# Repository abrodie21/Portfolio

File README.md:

# Design Portfolio

Here are two designs of personal projects that I have completed during my undergrad.

Design 1: Heartbeat Detection device, utilizing an IR emitter/sensor to measure the density of blood in a finger, signal processing to blink an LED with the hearbeat.

-This project was originally a Circuits II Lab project at Purdue (2k8) that I expanded upon to include a PCB schematic that can be fabricated.

Design 2: Powered Device sensor, utilizing a differential coil setup to detect magnetic fields in close proximity generated by transformers in power adapters. 

-Designed to be cheap and cost effective, utilizing a 1 layer PCB and as few components as possible.

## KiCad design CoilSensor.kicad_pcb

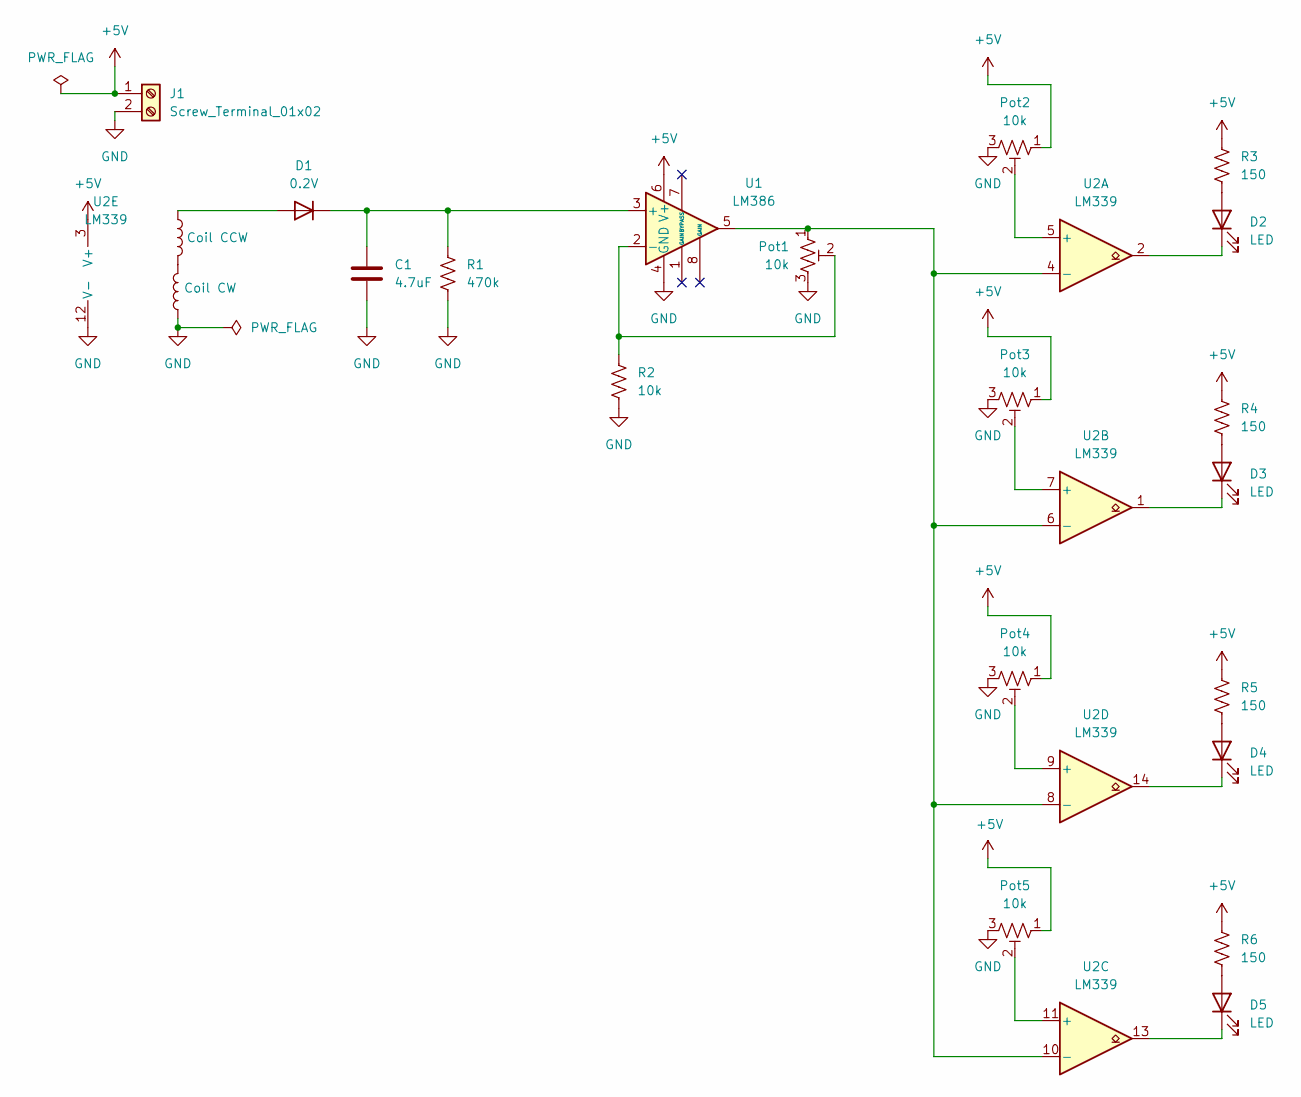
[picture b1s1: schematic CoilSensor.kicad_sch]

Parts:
C1: 4.7uF; CP_Elec_8x10.5
D1: 0.2V; D_5KPW_P7.62mm_Vertical_AnodeUp
D2, D3, D4, D5: LED; D_5KPW_P7.62mm_Vertical_AnodeUp
J1: Screw_Terminal_01x02; TerminalBlock_4Ucon_1x02_P3.50mm_Vertical
L1, L2: 2Pad
Pot1, Pot2, Pot3, Pot4, Pot5: 10k; Potentiometer_Vishay_T73XW_Horizontal
R1: 470k; R_Axial_DIN0414_L11.9mm_D4.5mm_P20.32mm_Horizontal
R2: 10k; R_Axial_DIN0414_L11.9mm_D4.5mm_P20.32mm_Horizontal
R3, R4, R5, R6: 150; R_Axial_DIN0414_L11.9mm_D4.5mm_P20.32mm_Horizontal
U1: LM386; DIP-8_W7.62mm_Socket_LongPads
U2: LM339; DIP-14_W7.62mm

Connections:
+5V: J1.1, Pot2.1, Pot3.1, Pot4.1, Pot5.1, R3.1, R4.1, R5.1, R6.1, U1.6 (V+), U2.3 (V+)
GND: C1.2, J1.2, L2.1, Pot1.3, Pot2.3, Pot3.3, Pot4.3, Pot5.3, R1.2, R2.2, U1.4 (GND), U2.12 (V-)
unnamed: D1.2 (A), L1.1
unnamed: C1.1, D1.1 (K), R1.1, U1.3 (+)
unnamed: D2.2 (A), R3.2
unnamed: D2.1 (K), U2.2
unnamed: D3.2 (A), R4.2
unnamed: D3.1 (K), U2.1
unnamed: D4.2 (A), R5.2
unnamed: D4.1 (K), U2.14
unnamed: D5.2 (A), R6.2
unnamed: D5.1 (K), U2.13
unnamed: L1.2, L2.2
unnamed: Pot1.2, R2.1, U1.2 (-)
unnamed: Pot2.2, U2.5 (+)
unnamed: Pot1.1, U1.5, U2.4 (-), U2.6 (-), U2.8 (-), U2.10 (-)
unnamed: Pot3.2, U2.7 (+)
unnamed: Pot5.2, U2.11 (+)
unnamed: Pot4.2, U2.9 (+)

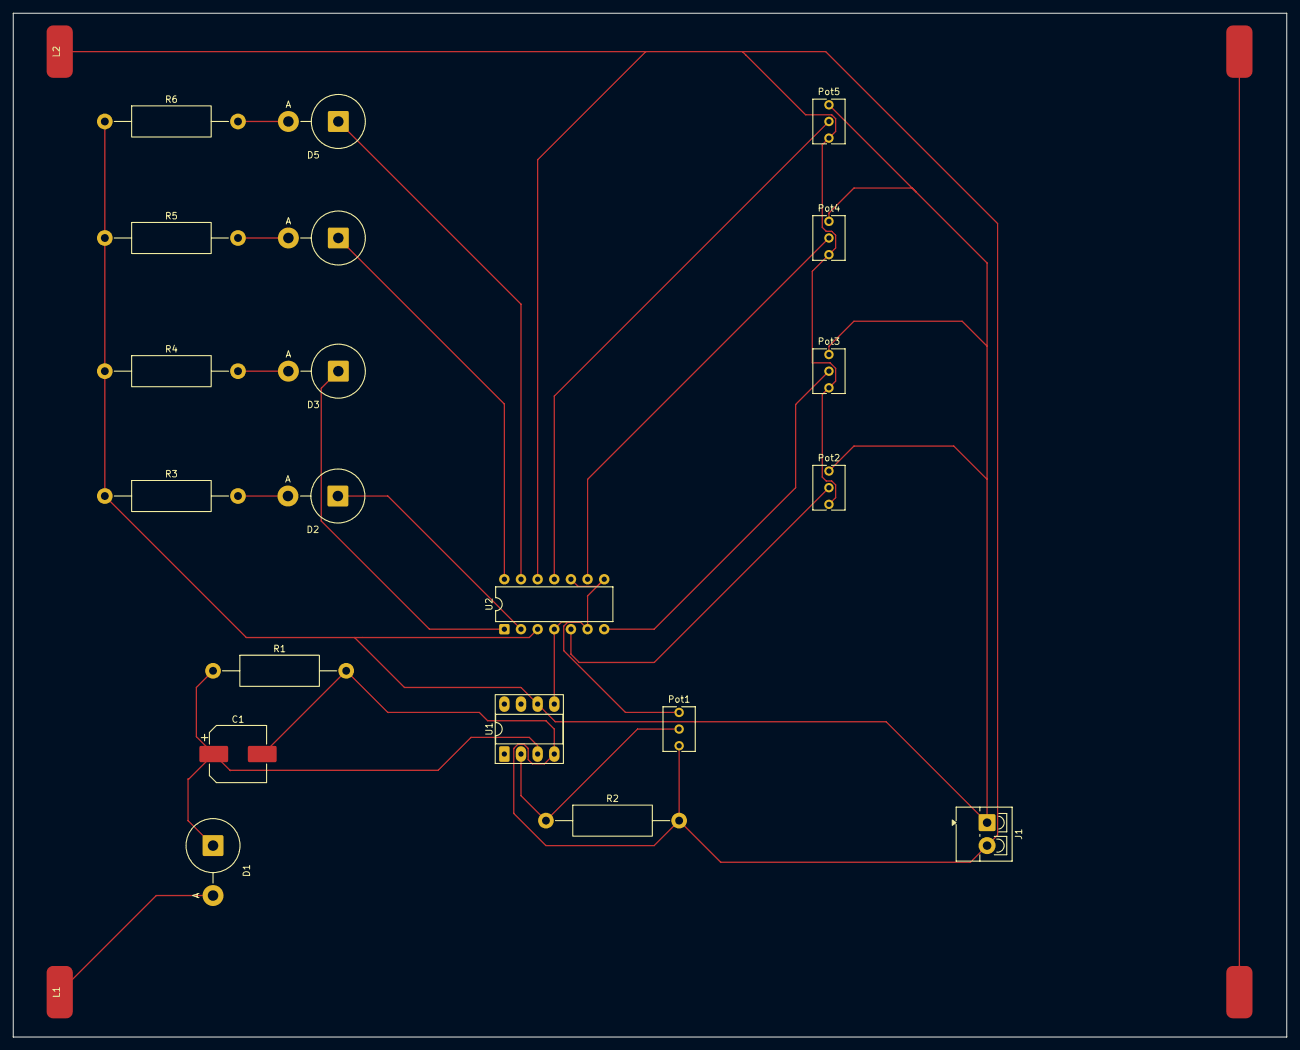
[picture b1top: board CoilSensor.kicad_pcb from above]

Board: 2 copper layers, 194.3 x 156.2 mm, 22 parts (0 on the bottom side), 19 nets.

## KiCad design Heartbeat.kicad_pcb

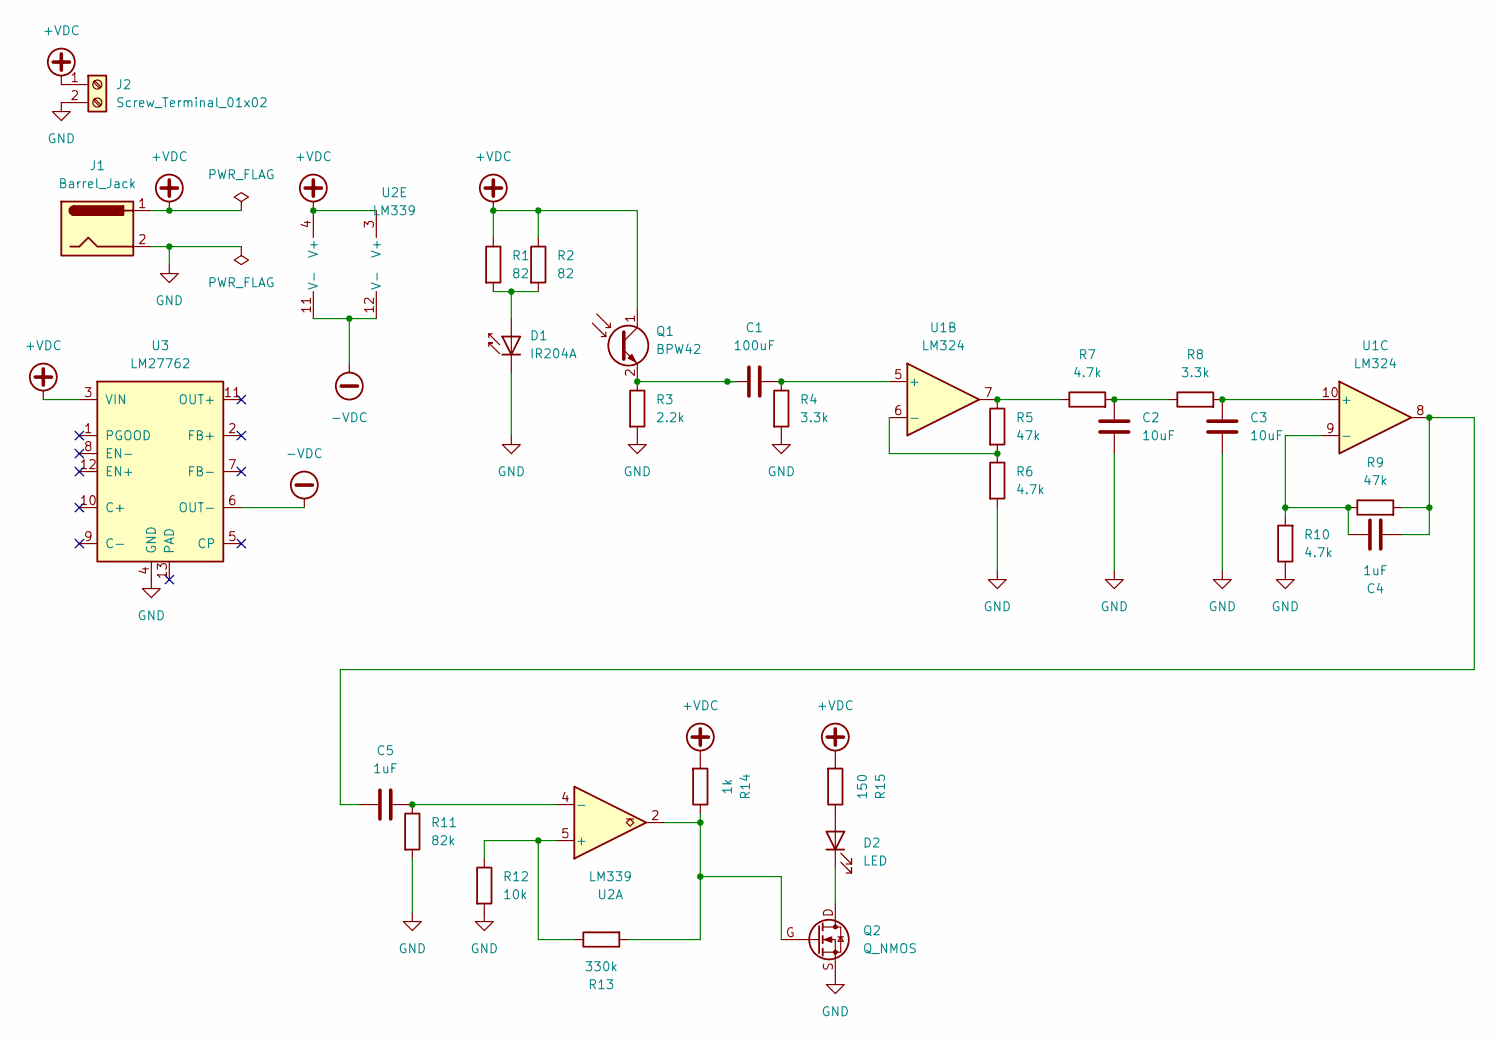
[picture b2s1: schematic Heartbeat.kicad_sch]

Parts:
C1: 100uF; CP_Axial_L11.0mm_D5.0mm_P18.00mm_Horizontal
C2, C3: 10uF; CP_Axial_L11.0mm_D5.0mm_P18.00mm_Horizontal
C4, C5: 1uF; CP_Axial_L11.0mm_D5.0mm_P18.00mm_Horizontal
D1: IR204A; D_DO-41_SOD81_P2.54mm_Vertical_AnodeUp
D2: LED; D_DO-41_SOD81_P2.54mm_Vertical_AnodeUp
J1: Barrel_Jack; BarrelJack_CUI_PJ-063AH_Horizontal_CircularHoles
J2: Screw_Terminal_01x02; TerminalBlock_4Ucon_1x02_P3.50mm_Vertical
Q1: BPW42; D_DO-41_SOD81_P2.54mm_Vertical_AnodeUp
Q2: Q_NMOS; TO-251-3_Vertical
R1, R2: 82; R_Axial_DIN0204_L3.6mm_D1.6mm_P5.08mm_Horizontal
R3: 2.2k; R_Axial_DIN0204_L3.6mm_D1.6mm_P5.08mm_Horizontal
R4, R8: 3.3k; R_Axial_DIN0204_L3.6mm_D1.6mm_P5.08mm_Horizontal
R5, R9: 47k; R_Axial_DIN0204_L3.6mm_D1.6mm_P5.08mm_Horizontal
R6, R7, R10: 4.7k; R_Axial_DIN0204_L3.6mm_D1.6mm_P5.08mm_Horizontal
R11: 82k; R_Axial_DIN0204_L3.6mm_D1.6mm_P5.08mm_Horizontal
R12: 10k; R_Axial_DIN0204_L3.6mm_D1.6mm_P5.08mm_Horizontal
R13: 330k; R_Axial_DIN0204_L3.6mm_D1.6mm_P5.08mm_Horizontal
R14: 1k; R_Axial_DIN0204_L3.6mm_D1.6mm_P5.08mm_Horizontal
R15: 150; R_Axial_DIN0204_L3.6mm_D1.6mm_P5.08mm_Horizontal
U1: LM324; DIP-14_W7.62mm
U2: LM339; SOIC-14_3.9x8.7mm_P1.27mm
U3: LM27762; WSON-12-1EP_3x2mm_P0.5mm_EP1x2.65_ThermalVias

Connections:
+VDC: J1.1, J2.1, Q1.1 (C), R1.1, R2.1, R14.2, R15.2, U1.4 (V+), U2.3 (V+), U3.3 (VIN)
-VDC: U1.11 (V-), U2.12 (V-), U3.6 (OUT-)
GND: C2.1, C3.1, D1.1 (K), J1.2, J2.2, Q2.S, R3.2, R4.2, R6.2, R10.1, R11.2, R12.2, U3.4 (GND); also elsewhere on the board
unnamed: C2.2, R7.2, R8.1
unnamed: C4.1, C5.1, R9.2, U1.8
unnamed: D1.2 (A), R1.2, R2.2
unnamed: D2.2 (A), R15.1
unnamed: D2.1 (K), Q2.D
unnamed: C1.1, Q1.2 (E), R3.1
unnamed: Q2.G, R13.2, R14.1, U2.2
unnamed: R5.1, R7.1, U1.7
unnamed: C1.2, R4.1, U1.5 (+)
unnamed: R5.2, R6.1, U1.6 (-)
unnamed: C3.2, R8.2, U1.10 (+)
unnamed: C4.2, R9.1, R10.2, U1.9 (-)
unnamed: R12.1, R13.1, U2.5 (+)
unnamed: C5.2, R11.1, U2.4 (-)

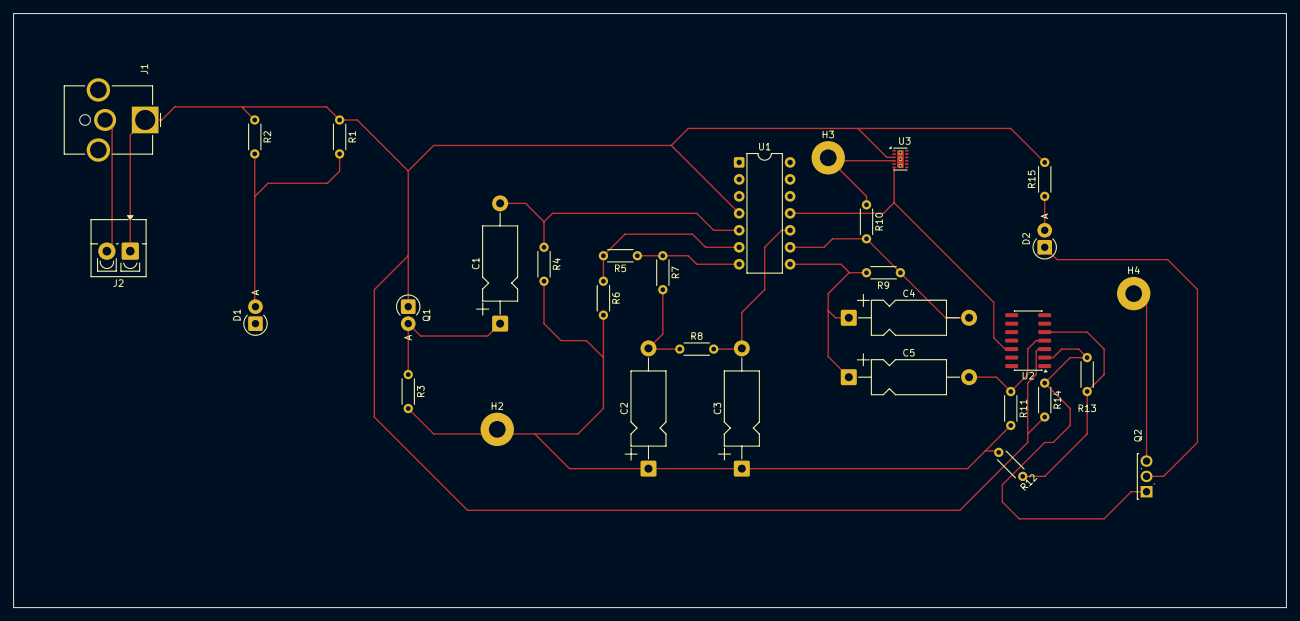
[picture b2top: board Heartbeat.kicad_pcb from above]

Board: 2 copper layers, 190.5 x 88.9 mm, 32 parts (0 on the bottom side), 17 nets.

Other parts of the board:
H2, H3, H4: MountingHole_Pad; MountingHole_2.5mm_Pad

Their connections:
GND: H2.1, H3.1, H4.1; also elsewhere on the board
